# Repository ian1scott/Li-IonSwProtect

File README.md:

# Li-IonSwProtect
Add-on board for projects to use a Li-Ion battery and have undervoltage protection and a push-button on-off switch

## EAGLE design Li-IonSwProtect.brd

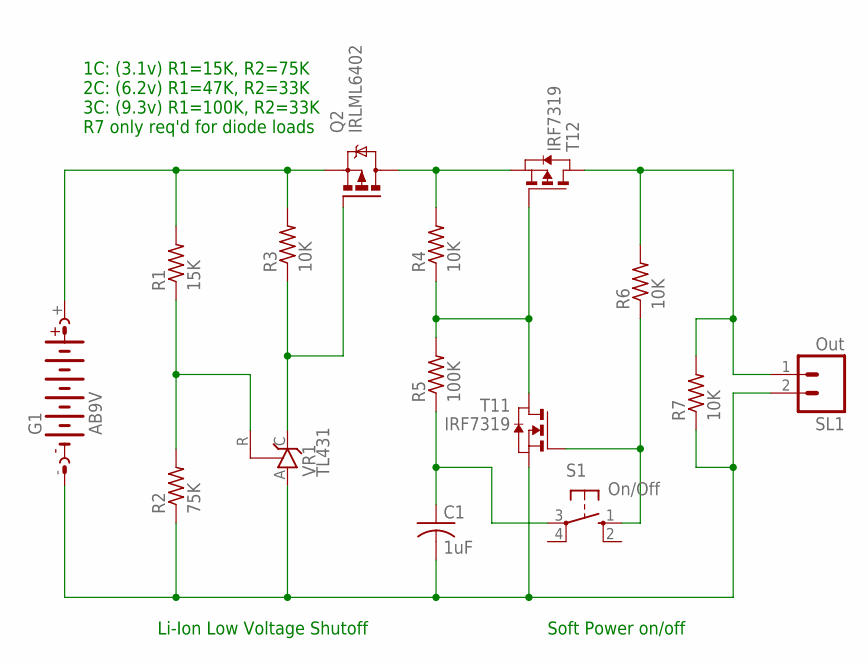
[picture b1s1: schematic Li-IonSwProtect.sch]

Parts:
C1: 1uF; C0805
G1: AB9V
Q2: IRLML6402; MICRO3
R1: 15K; R0805
R2: 75K; R0805
R3, R4, R6, R7: 10K; R0805
R5: 100K; R0805
S1: On/Off; B3F-10XX
SL1: Out; 02P
T1: IRF7319; SO8
VR1: TL431; TO92-CLP

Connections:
unnamed: G1.+, Q2.2 (S), R1.2, R3.2
unnamed: R1.1, R2.2, VR1.R
unnamed: C1.2, G1.-, R2.1, R7.1, SL1.2, T1.1 (S), VR1.A
unnamed: Q2.3 (D), R4.2, T1.3 (S)
unnamed: R4.1, R5.2, T1.4 (G), T1.7 (D), T1.8 (D)
unnamed: C1.1, R5.1, S1.3
unnamed: Q2.1 (G), R3.1, VR1.C
unnamed: R6.1, S1.1 (S), T1.2 (G)
unnamed: R6.2, R7.2, SL1.1, T1.5 (D), T1.6 (D)

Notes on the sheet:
Li-Ion Low Voltage Shutoff
Soft Power on/off
1C: (3.1v) R1=15K, R2=75K 2C: (6.2v) R1=47K, R2=33K 3C: (9.3v) R1=100K, R2=33K R7 only req'd for diode loads

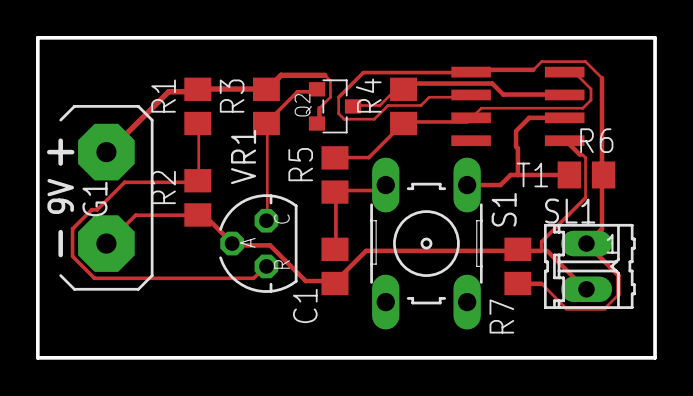
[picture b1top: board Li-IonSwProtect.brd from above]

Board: 2 copper layers, 34.3 x 17.8 mm, 14 parts (0 on the bottom side), 9 nets.

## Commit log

2018-02-02 Add files via upload
    Added a BOM
